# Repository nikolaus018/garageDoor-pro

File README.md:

# garageDoor-pro

**A small box in the car that opens the garage door by itself when you leave home and when you arrive.**
No phone, no app: an ESP32-C3, a GPS module and one transistor that presses the button of a spare
remote, powered over USB-C from the car. Home is set once from a small Wi-Fi web panel.

## How it works

The car's USB socket switches off with the ignition, so the board boots when the car starts and
loses power when it stops. The underground garage has no GPS reception, so the board remembers in
flash where the car was last parked.

| State at boot | What happens |
|---|---|
| Parked at home | Presses the remote 10× (every 2 s) while you drive out, then switches to *away* once the GPS is past the leave radius |
| Parked away | Waits for a GPS fix |
| Away, inside the arrive radius | Presses every 2 s for up to 180 s, saves *home* |
| Drove past home | Detects leaving the radius again and stops pressing |

Two radii (150 m arrive, 300 m leave by default, both configurable) stop GPS jitter at the edge from
flapping the state. A fix only counts with `gnssFixOK`, ≤ 50 m accuracy and ≥ 4 satellites. The
state machine is pure C and unit-tested on the host with AddressSanitizer and UBSan.

## Two ways to build it

| | Prototype | Custom PCB |
|---|---|---|
| Parts | ESP32-C3 SuperMini, GPS module, NPN, a few resistors | ESP32-C3-MINI-1 on a 4-layer board, assembled by JLCPCB |
| Effort | About an hour on perfboard | Order Gerbers, BOM and CPL as provided |
| Guide | [prototype/README.md](prototype/README.md) | [hardware/ORDERING.md](hardware/ORDERING.md) |

Both run the same firmware.

## Documentation

| | |
|---|---|
| [prototype/](prototype/README.md) | Perfboard build: parts, layout, assembly, bench test, 3D-printable case |
| [docs/user-guide.md](docs/user-guide.md) | Installing in the car and setting it up |
| [docs/design.md](docs/design.md) | Behaviour, parts, circuit and PCB decisions |
| [firmware/README.md](firmware/README.md) | Build, flash, OTA, LED codes |
| [hardware/](hardware/ORDERING.md) | KiCad project, Gerbers, BOM, CPL, schematic PDF, STEP model |

## Repository layout

```
firmware/    ESP-IDF project (GNSS, trip state machine, captive-portal web panel, OTA, host tests)
hardware/    KiCad design; gen/ holds the Python generator, netlist.py is the single source
prototype/   perfboard build guide, wiring diagrams, 3D-printable case
docs/        design notes and user guide
```

## Quick start

```bash
cd firmware && . ~/esp/esp-idf/export.sh && idf.py build flash
```

Run the host unit tests with `firmware/test/run.sh`.

## License

[MIT](LICENSE). Espressif symbol and 3D files in `hardware/lib/` keep their own license.

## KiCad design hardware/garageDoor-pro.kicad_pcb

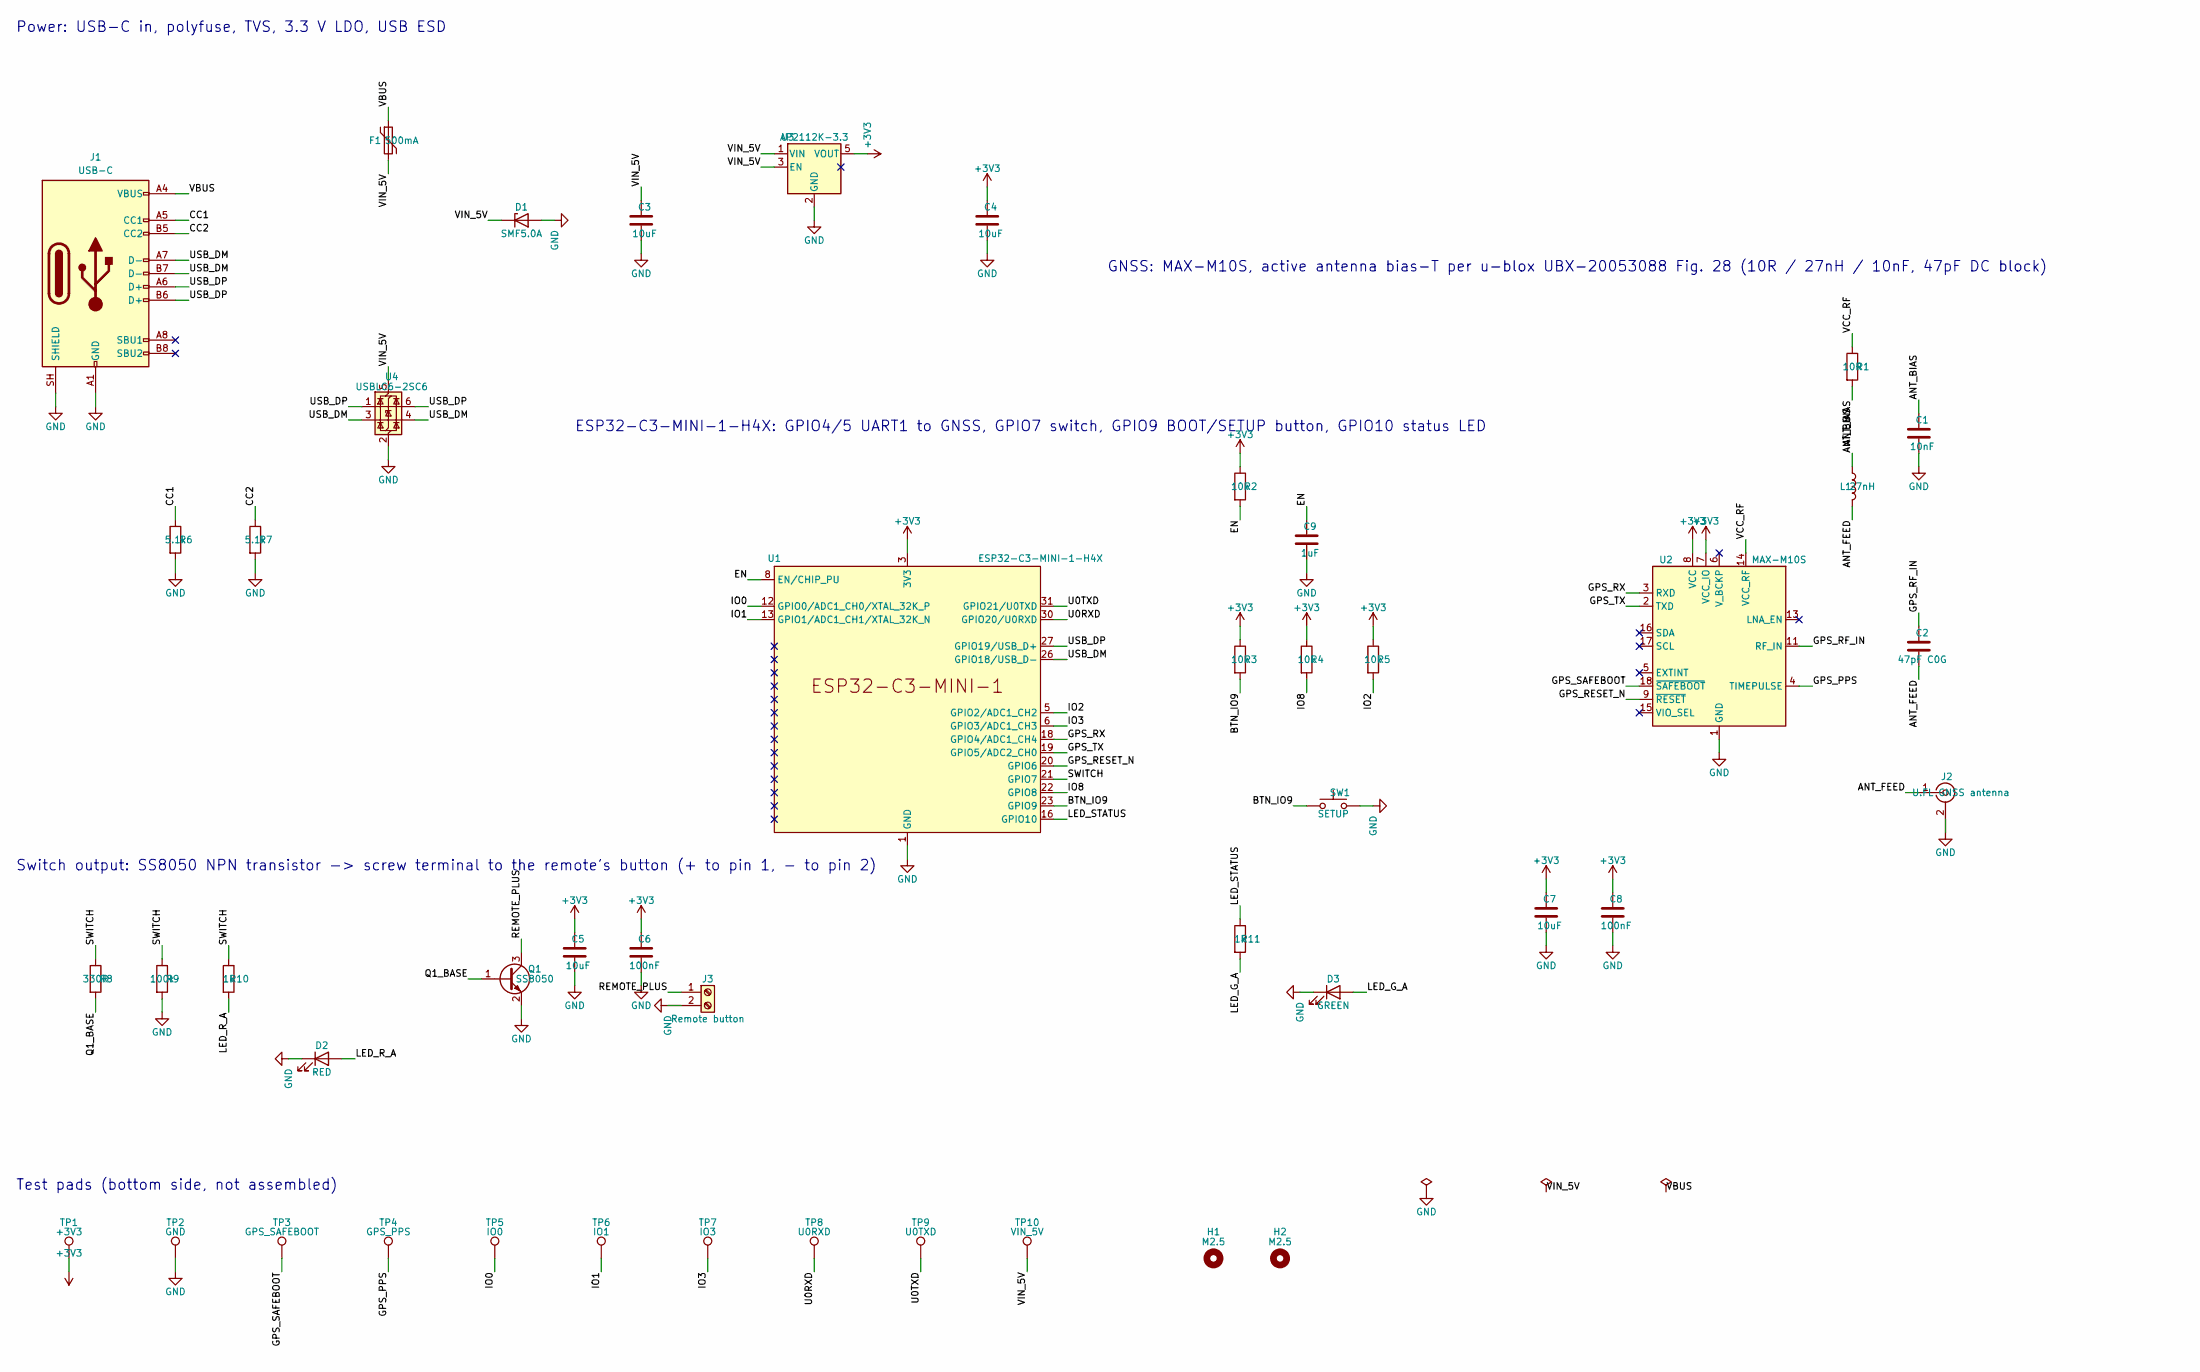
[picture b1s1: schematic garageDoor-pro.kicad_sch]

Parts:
C1: 10nF; C_0402_1005Metric; MPN CL05B103KB5NNNC; LCSC C15195
C2: 47pF C0G; C_0402_1005Metric; MPN 0402CG470J500NT; LCSC C1567
C3, C4, C5, C7: 10uF; C_0603_1608Metric; MPN CL10A106KP8NNNC; LCSC C19702
C6, C8: 100nF; C_0402_1005Metric; MPN CC0402KRX7R7BB104; LCSC C60474
C9: 1uF; C_0402_1005Metric; MPN CL05A105KP5NNNC; LCSC C14445
D1: SMF5.0A; D_SOD-123F; MPN SMF5.0A; LCSC C1509112
D2: RED; LED_0603_1608Metric; MPN KT-0603R; LCSC C2286
D3: GREEN; LED_0603_1608Metric; MPN KT-0603G; LCSC C12624
F1: 500mA; Fuse_1206_3216Metric; MPN SMD1206-050C-6V; LCSC C22472478
H1, H2: M2.5; MountingHole_2.7mm_M2.5
J1: USB-C; USB_C_Receptacle_HRO_TYPE-C-31-M-12; MPN TYPE-C-31-M-12; LCSC C165948
J2: U.FL GNSS antenna; U.FL_Hirose_U.FL-R-SMT-1_Vertical; MPN U.FL-R-SMT-1(10); LCSC C88373
J3: Remote button; TerminalBlock_Phoenix_MKDS-1,5-2-5.08_1x02_P5.08mm_Horizont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; MPN KF128-5.08-2P; LCSC C474952
L1: 27nH; L_0402_1005Metric; MPN LQG15HS27NJ02D; LCSC C12669
Q1: SS8050; SOT-23; MPN SS8050; LCSC C2150
R1: 10R; R_1206_3216Metric; MPN 1206W4F100JT5E; LCSC C17903
R2, R3, R4, R5: 10k; R_0402_1005Metric; MPN 0402WGF1002TCE; LCSC C25744
R6, R7: 5.1k; R_0402_1005Metric; MPN 0402WGF5101TCE; LCSC C25905
R8: 330R; R_0402_1005Metric; MPN 0402WGF3300TCE; LCSC C25104
R9: 100k; R_0402_1005Metric; MPN 0402WGF1003TCE; LCSC C25741
R10, R11: 1k; R_0603_1608Metric; MPN 0603WAF1001T5E; LCSC C21190
SW1: SETUP; SW_Push_1P1T_XKB_TS-1187A; MPN TS-1187A-B-A-B; LCSC C318884
TP1: +3V3; TestPoint_Pad_D1.0mm
TP2: GND; TestPoint_Pad_D1.0mm
TP3: GPS_SAFEBOOT; TestPoint_Pad_D1.0mm
TP4: GPS_PPS; TestPoint_Pad_D1.0mm
TP5: IO0; TestPoint_Pad_D1.0mm
TP6: IO1; TestPoint_Pad_D1.0mm
TP7: IO3; TestPoint_Pad_D1.0mm
TP8: U0RXD; TestPoint_Pad_D1.0mm
TP9: U0TXD; TestPoint_Pad_D1.0mm
TP10: VIN_5V; TestPoint_Pad_D1.0mm
U1: ESP32-C3-MINI-1-H4X; ESP32-C3-MINI-1; MPN ESP32-C3-MINI-1-H4X; LCSC C41349510
U2: MAX-M10S; ublox_MAX; MPN MAX-M10S-00B; LCSC C4153167
U3: AP2112K-3.3; SOT-23-5; MPN AP2112K-3.3TRG1; LCSC C51118
U4: USBLC6-2SC6; SOT-23-6; MPN USBLC6-2SC6; LCSC C7519

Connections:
+3V3: C4.1, C5.1, C6.1, C7.1, C8.1, R2.1, R3.1, R4.1, R5.1, TP1.1, U1.3 (3V3), U2.7 (VCC_IO), U2.8 (VCC), U3.5 (VOUT)
/ANT_BIAS: C1.1, L1.1, R1.2
/ANT_FEED: C2.2, J2.1 (In), L1.2
/BTN_IO9: R3.2, SW1.1, U1.23 (GPIO9)
/CC1: J1.A5 (CC1), R6.1
/CC2: J1.B5 (CC2), R7.1
/EN: C9.1, R2.2, U1.8 (EN/CHIP_PU)
/GPS_PPS: TP4.1, U2.4 (TIMEPULSE)
/GPS_RESET_N: U1.20 (GPIO6), U2.9 (~RESET)
/GPS_RF_IN: C2.1, U2.11 (RF_IN)
/GPS_RX: U1.18 (GPIO4/ADC1_CH4), U2.3 (RXD)
/GPS_SAFEBOOT: TP3.1, U2.18 (~SAFEBOOT)
/GPS_TX: U1.19 (GPIO5/ADC2_CH0), U2.2 (TXD)
/IO0: TP5.1, U1.12 (GPIO0/ADC1_CH0/XTAL_32K_P)
/IO1: TP6.1, U1.13 (GPIO1/ADC1_CH1/XTAL_32K_N)
/IO2: R5.2, U1.5 (GPIO2/ADC1_CH2)
/IO3: TP7.1, U1.6 (GPIO3/ADC1_CH3)
/IO8: R4.2, U1.22 (GPIO8)
/LED_G_A: D3.2 (A), R11.2
/LED_R_A: D2.2 (A), R10.2
/LED_STATUS: R11.1, U1.16 (GPIO10)
/Q1_BASE: Q1.1 (B), R8.2
/REMOTE_PLUS: J3.1, Q1.3 (C)
/SWITCH: R8.1, R9.1, R10.1, U1.21 (GPIO7)
/U0RXD: TP8.1, U1.30 (GPIO20/U0RXD)
/U0TXD: TP9.1, U1.31 (GPIO21/U0TXD)
/USB_DM: J1.A7 (D-), J1.B7 (D-), U1.26 (GPIO18/USB_D-), U4.3 (I/O2), U4.4 (I/O2)
/USB_DP: J1.A6 (D+), J1.B6 (D+), U1.27 (GPIO19/USB_D+), U4.1 (I/O1), U4.6 (I/O1)
/VBUS: F1.1, J1.A4 (VBUS), J1.A9 (VBUS), J1.B4 (VBUS), J1.B9 (VBUS)
/VCC_RF: R1.1, U2.14 (VCC_RF)
/VIN_5V: C3.1, D1.1 (K), F1.2, TP10.1, U3.1 (VIN), U3.3 (EN), U4.5 (VBUS)
GND: C1.2, C3.2, C4.2, C5.2, C6.2, C7.2, C8.2, C9.2, D1.2 (A), D2.1 (K), D3.1 (K), J1.A1 (GND), J1.A12 (GND), J1.B1 (GND), J1.B12 (GND), J1.SH (SHIELD), J2.2 (Ext), J3.2, Q1.2 (E), R6.2, R7.2, R9.2, SW1.2, TP2.1, U1.1 (GND), U1.2 (GND), U1.11 (GND), U1.14 (GND), U1.36 (GND), U1.37 (GND), U1.38 (GND), U1.39 (GND), U1.40 (GND), U1.41 (GND), U1.42 (GND), U1.43 (GND), U1.44 (GND), U1.45 (GND), U1.46 (GND), U1.47 (GND), U1.48 (GND), U1.49 (GND), U1.50 (GND), U1.51 (GND), U1.52 (GND), U1.53 (GND), U2.1 (GND), U2.10 (GND), U2.12 (GND), U3.2 (GND), U4.2 (GND)

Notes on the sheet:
Power: USB-C in, polyfuse, TVS, 3.3 V LDO, USB ESD
ESP32-C3-MINI-1-H4X: GPIO4/5 UART1 to GNSS, GPIO7 switch, GPIO9 BOOT/SETUP button, GPIO10 status LED
GNSS: MAX-M10S, active antenna bias-T per u-blox UBX-20053088 Fig. 28 (10R / 27nH / 10nF, 47pF DC block)
Switch output: SS8050 NPN transistor -> screw terminal to the remote's button (+ to pin 1, - to pin 2)
Test pads (bottom side, not assembled)

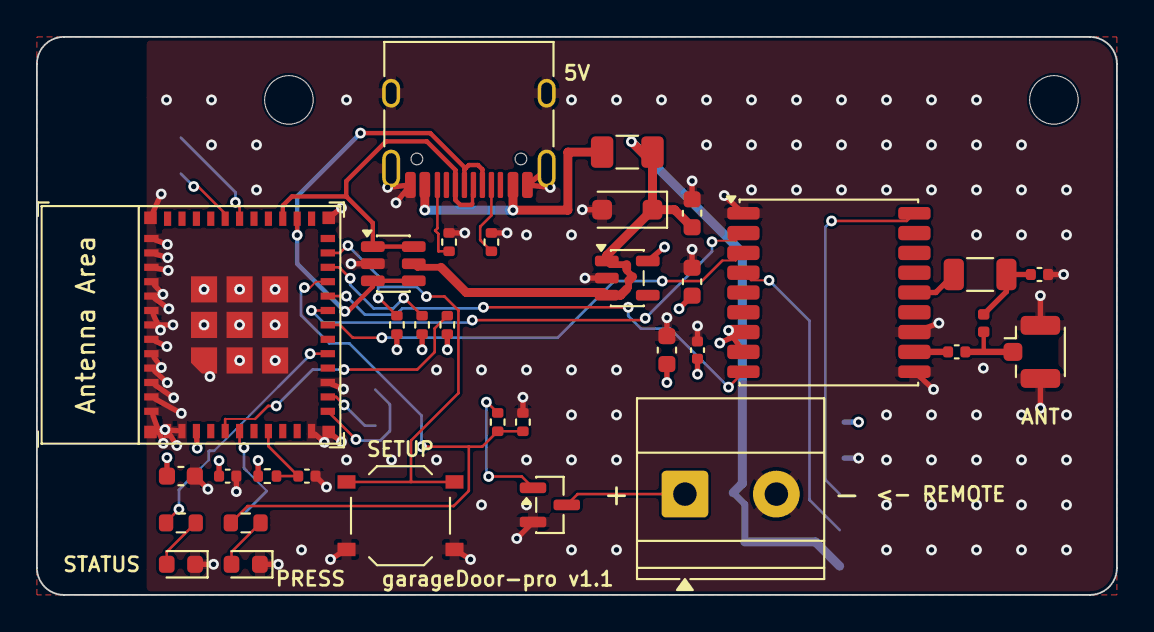
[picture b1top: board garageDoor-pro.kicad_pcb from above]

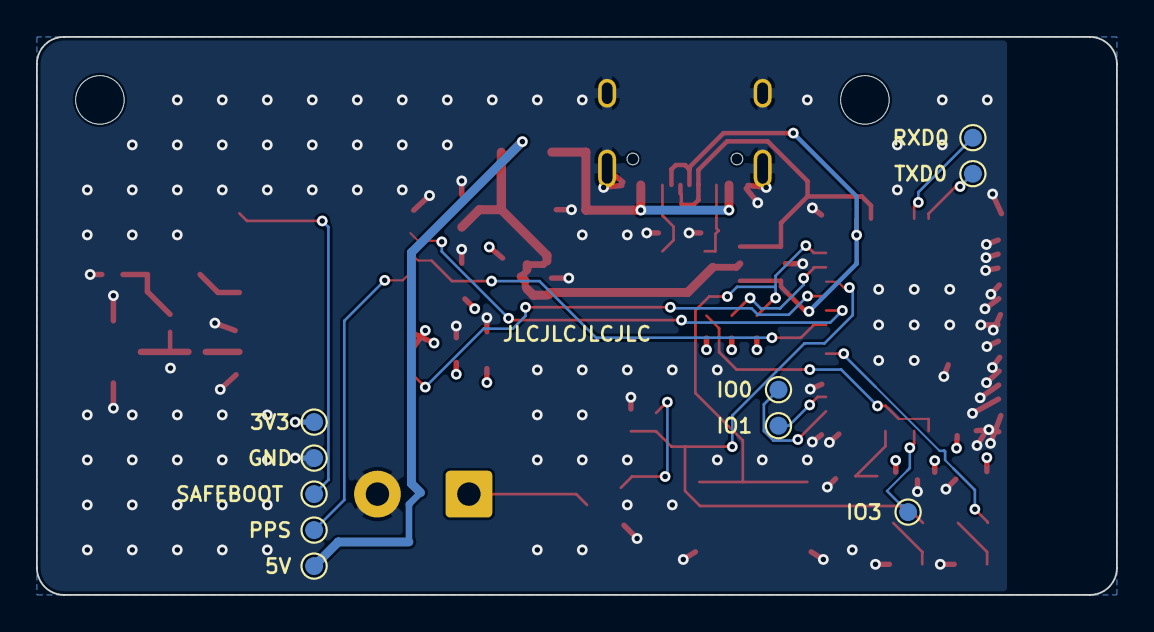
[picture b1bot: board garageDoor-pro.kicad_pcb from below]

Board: 4 copper layers, 60.0 x 31.0 mm, 46 parts (10 on the bottom side), 32 nets.

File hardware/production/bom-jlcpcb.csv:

Comment,Designator,Footprint,LCSC Part #,Manufacturer Part,Quantity
10nF,C1,C_0402_1005Metric,C15195,CL05B103KB5NNNC,1
47pF C0G,C2,C_0402_1005Metric,C1567,0402CG470J500NT,1
10uF,"C3,C4,C5,C7",C_0603_1608Metric,C19702,CL10A106KP8NNNC,4
100nF,"C6,C8",C_0402_1005Metric,C60474,CC0402KRX7R7BB104,2
1uF,C9,C_0402_1005Metric,C14445,CL05A105KP5NNNC,1
SMF5.0A,D1,D_SOD-123F,C1509112,SMF5.0A,1
RED,D2,LED_0603_1608Metric,C2286,KT-0603R,1
GREEN,D3,LED_0603_1608Metric,C12624,KT-0603G,1
500mA,F1,Fuse_1206_3216Metric,C22472478,SMD1206-050C-6V,1
USB-C,J1,USB_C_Receptacle_HRO_TYPE-C-31-M-12,C165948,TYPE-C-31-M-12,1
U.FL GNSS antenna,J2,U.FL_Hirose_U.FL-R-SMT-1_Vertical,C88373,U.FL-R-SMT-1(10),1
Remote button,J3,"TerminalBlock_Phoenix_MKDS-1,5-2-5.08_1x02_P5.08mm_Horizontal",C474952,KF128-5.08-2P,1
27nH,L1,L_0402_1005Metric,C12669,LQG15HS27NJ02D,1
SS8050,Q1,SOT-23,C2150,SS8050,1
10R,R1,R_1206_3216Metric,C17903,1206W4F100JT5E,1
10k,"R2,R3,R4,R5",R_0402_1005Metric,C25744,0402WGF1002TCE,4
5.1k,"R6,R7",R_0402_1005Metric,C25905,0402WGF5101TCE,2
330R,R8,R_0402_1005Metric,C25104,0402WGF3300TCE,1
100k,R9,R_0402_1005Metric,C25741,0402WGF1003TCE,1
1k,"R10,R11",R_0603_1608Metric,C21190,0603WAF1001T5E,2
SETUP,SW1,SW_Push_1P1T_XKB_TS-1187A,C318884,TS-1187A-B-A-B,1
ESP32-C3-MINI-1-H4X,U1,ESP32-C3-MINI-1,C41349510,ESP32-C3-MINI-1-H4X,1
MAX-M10S,U2,ublox_MAX,C4153167,MAX-M10S-00B,1
AP2112K-3.3,U3,SOT-23-5,C51118,AP2112K-3.3TRG1,1
USBLC6-2SC6,U4,SOT-23-6,C7519,USBLC6-2SC6,1

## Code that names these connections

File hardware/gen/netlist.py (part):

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    "R1": ("10R", "Device:R", "Resistor_SMD:R_1206_3216Metric",
           "C17903", "1206W4F100JT5E", "Antenna supply current limit 0.25 W"),
    "R2": ("10k", "Device:R", "Resistor_SMD:R_0402_1005Metric", "C25744", "0402WGF1002TCE", "EN pull-up"),
    "R3": ("10k", "Device:R", "Resistor_SMD:R_0402_1005Metric", "C25744", "0402WGF1002TCE", "GPIO9 pull-up"),
    "R4": ("10k", "Device:R", "Resistor_SMD:R_0402_1005Metric", "C25744", "0402WGF1002TCE", "GPIO8 pull-up"),
    "R5": ("10k", "Device:R", "Resistor_SMD:R_0402_1005Metric", "C25744", "0402WGF1002TCE", "GPIO2 pull-up"),
    "R6": ("5.1k", "Device:R", "Resistor_SMD:R_0402_1005Metric", "C25905", "0402WGF5101TCE", "CC1 pull-down"),
    "R7": ("5.1k", "Device:R", "Resistor_SMD:R_0402_1005Metric", "C25905", "0402WGF5101TCE", "CC2 pull-down"),
    "R8": ("330R", "Device:R", "Resistor_SMD:R_0402_1005Metric", "C25104", "0402WGF3300TCE", "Transistor base current"),
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    "SWITCH": [("U1", "21"), ("R8", "1"), ("R9", "1"), ("R10", "1")],
    "Q1_BASE": [("R8", "2"), ("Q1", "1")],
    "LED_R_A": [("R10", "2"), ("D2", "2")],
    "REMOTE_PLUS": [("Q1", "3"), ("J3", "1")],   # collector; J3 pin 2 is GND (emitter)
    "GPS_TX": [("U2", "2"), ("U1", "19")],     # GNSS TXD -> ESP GPIO5 (UART1 RX)
    "GPS_RX": [("U2", "3"), ("U1", "18")],     # GNSS RXD <- ESP GPIO4 (UART1 TX)
    "GPS_RESET_N": [("U2", "9"), ("U1", "20")],
    "GPS_PPS": [("U2", "4"), ("TP4", "1")],
    "GPS_SAFEBOOT": [("U2", "18"), ("TP3", "1")],
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

def pcb_net_name(net):
    """KiCad names nets from local schematic labels with the sheet path, e.g. /USB_DP."""
    return net if net in POWER_NETS else "/" + net


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
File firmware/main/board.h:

// Pin maps. Pick the board in menuconfig ("garageDoor" -> "Board"); see prototype/README.md.
#pragma once

#include "driver/gpio.h"
#include "sdkconfig.h"

#define GNSS_UART UART_NUM_1

#if CONFIG_GARAGE_BOARD_PCB_V1
// garageDoor-pro PCB (hardware/gen/netlist.py)
#define PIN_GPS_TX_TO_GNSS   GPIO_NUM_4   // UART1 TX -> receiver RXD
#define PIN_GPS_RX_FROM_GNSS GPIO_NUM_5   // UART1 RX <- receiver TXD
#define PIN_GPS_RESET_N      GPIO_NUM_6   // open-drain, low >= 1 ms resets the receiver
#define HAS_GPS_RESET        1
#define PIN_SWITCH           GPIO_NUM_7   // high turns the transistor on (remote button) + red LED
#define PIN_BUTTON           GPIO_NUM_9   // BOOT / SETUP, active low
#define PIN_LED_STATUS       GPIO_NUM_10
#define LED_ACTIVE_LOW       0

#elif CONFIG_GARAGE_BOARD_C3_SUPERMINI
// ESP32-C3 SuperMini: on-board BOOT button (GPIO9) and blue LED (GPIO8, lights when low)
#define PIN_GPS_TX_TO_GNSS   GPIO_NUM_4
#define PIN_GPS_RX_FROM_GNSS GPIO_NUM_5
#define HAS_GPS_RESET        0            // GPS modules usually don't bring out reset
#define PIN_SWITCH           GPIO_NUM_7
#define PIN_BUTTON           GPIO_NUM_9
#define PIN_LED_STATUS       GPIO_NUM_8
#define LED_ACTIVE_LOW       1

#elif CONFIG_GARAGE_BOARD_S3_DEVKIT
// ESP32-S3 DevKitC: BOOT button on GPIO0; its RGB LED needs a driver, so use an external LED
#define PIN_GPS_TX_TO_GNSS   GPIO_NUM_4
#define PIN_GPS_RX_FROM_GNSS GPIO_NUM_5
#define HAS_GPS_RESET        0
#define PIN_SWITCH           GPIO_NUM_7
#define PIN_BUTTON           GPIO_NUM_0
#define PIN_LED_STATUS       GPIO_NUM_10  // optional: LED + 1k to GND
#define LED_ACTIVE_LOW       0

#else
#error "No garageDoor board selected (menuconfig: garageDoor -> Board)"
#endif

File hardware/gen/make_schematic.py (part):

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TP_ROW_Y = 264.16
TEXTS = [
    ("Power: USB-C in, polyfuse, TVS, 3.3 V LDO, USB ESD", 30.48, 30.48),
    ("ESP32-C3-MINI-1-H4X: GPIO4/5 UART1 to GNSS, GPIO7 switch, GPIO9 BOOT/SETUP button, GPIO10 status LED",
     137.16, 106.68),
    ("GNSS: MAX-M10S, active antenna bias-T per u-blox UBX-20053088 Fig. 28 (10R / 27nH / 10nF, 47pF DC block)",
     238.76, 76.2),
    ("Switch output: SS8050 NPN transistor -> screw terminal to the remote's button (+ to pin 1, - to pin 2)", 30.48, 190.5),
    ("Test pads (bottom side, not assembled)", 30.48, 251.46),
]

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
